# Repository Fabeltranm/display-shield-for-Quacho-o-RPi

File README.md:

# display-shield-for-Quacho-o-RPi

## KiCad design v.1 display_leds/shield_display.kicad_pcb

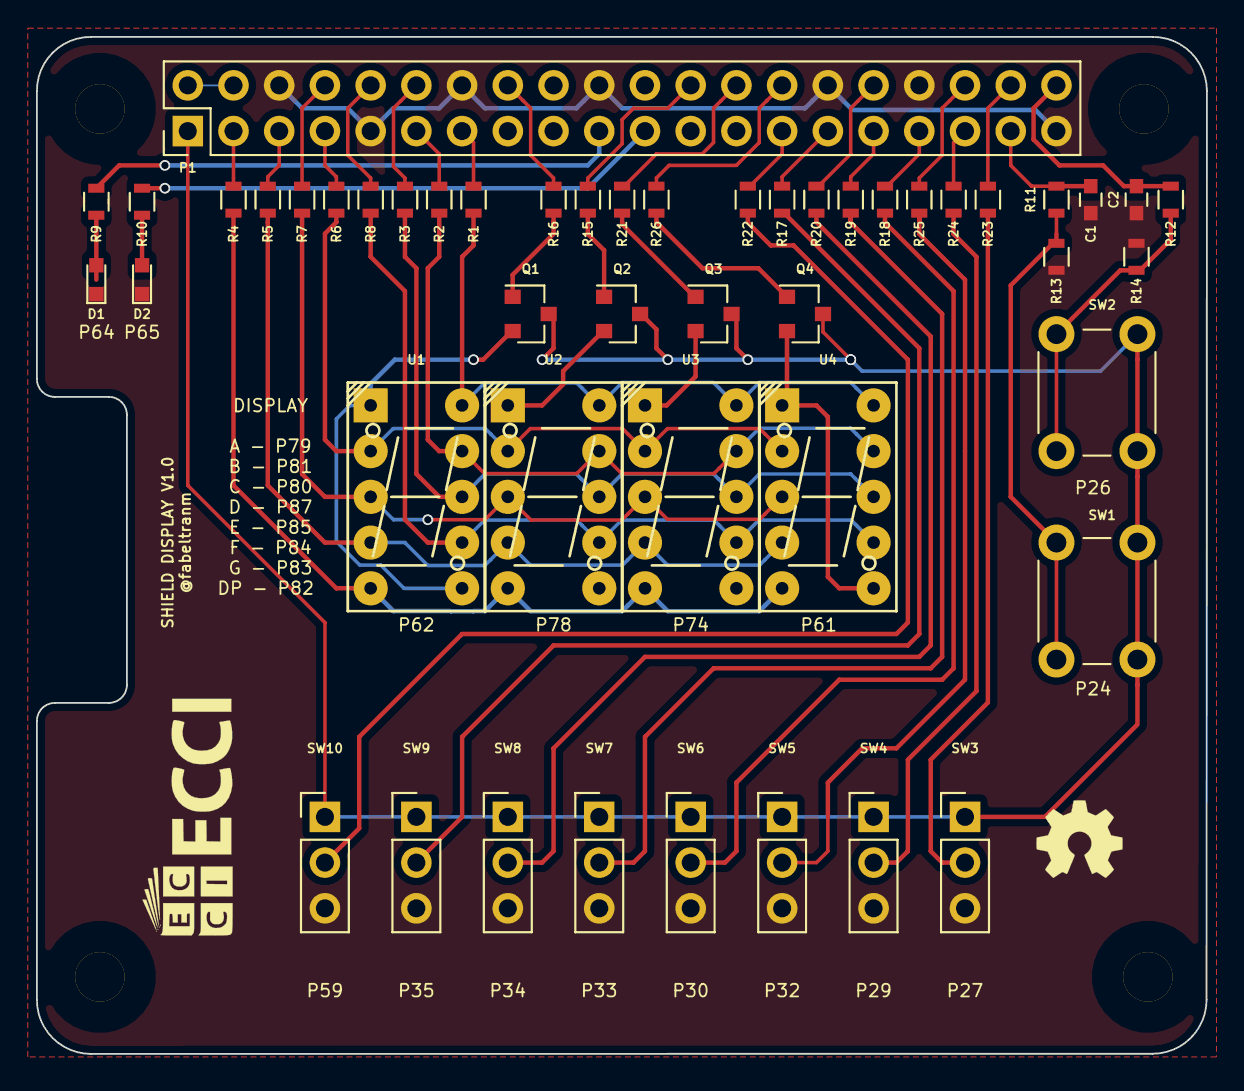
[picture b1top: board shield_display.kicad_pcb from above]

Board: 2 copper layers, 65.0 x 56.5 mm, 49 parts (0 on the bottom side), 55 nets.

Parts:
C1, C2: 0.1u; C_0603
D1, D2: LED; LED_0603
P1: CONN_02X20; Pin_Header_Straight_2x20_Pitch2.54mm
Q1, Q2, Q3, Q4: MMBT3906; SOT-23
R1, R2, R3, R4, R5, R6, R7, R8: 100; R_0603
R9, R10: 390; R_0603
R11, R12, R13, R14, R17, R18, R19, R20, R22, R23, R24, R25: 10K; R_0603
R15, R16, R21, R26: 2.2k; R_0603
SW1, SW2: PTS645SM43SMTR92 LFS; SW_PUSH_6mm
SW3, SW4, SW5, SW6, SW7, SW8, SW9, SW10: EG1218; Pin_Header_Straight_1x03_Pitch2.54mm
U1, U2, U3, U4: HDSP-7501; HDSP-78xx

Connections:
+3V3: P1.1, Q1.3, Q2.3, Q3.3, Q4.3, SW1.2, SW2.2, SW3.1, SW4.1, SW5.1, SW6.1, SW7.1, SW8.1, SW9.1, SW10.1
+5V: P1.2, P1.4
A: R1.1, U1.10, U2.10, U3.10, U4.10
B: R2.1, U1.9, U2.9, U3.9, U4.9
C: R3.1, U1.8, U2.8, U3.8, U4.8
D: R4.1, U1.5, U2.5, U3.5, U4.5
DP: R8.1, U1.7, U2.7, U3.7, U4.7
E: R5.1, U1.4, U2.4, U3.4, U4.4
F_: R6.1, U1.2, U2.2, U3.2, U4.2
G: R7.1, U1.3, U2.3, U3.3, U4.3
GND: C1.2, C2.2, D1.1, D2.1, P1.6, P1.9, P1.14, P1.20, P1.30, P1.34, P1.39, R13.1, R14.1, SW3.3, SW4.3, SW5.3, SW6.3, SW7.3, SW8.3, SW9.3, SW10.3
unnamed: D1.2, R9.1
unnamed: D2.2, R10.1
unnamed: Q1.1, R16.1
unnamed: Q1.2, U1.1, U1.6
unnamed: Q2.1, R15.1
unnamed: Q2.2, U2.1, U2.6
unnamed: Q3.1, R21.1
unnamed: Q3.2, U3.1, U3.6
unnamed: Q4.1, R26.1
unnamed: Q4.2, U4.1, U4.6
unnamed: R11.1, R13.2, SW1.1
unnamed: R12.1, R14.2, SW2.1
unnamed: R17.1, SW9.2
unnamed: R18.1, SW6.2
unnamed: R19.1, SW7.2
unnamed: R20.1, SW8.2
unnamed: R22.1, SW10.2
unnamed: R23.1, SW3.2
unnamed: R24.1, SW4.2
unnamed: R25.1, SW5.2
P024: C2.1, P1.40, R12.2
P026: C1.1, P1.37, R11.2
P027: P1.38, R23.2
P029: P1.35, R24.2
P030: P1.33, R18.2
P032: P1.36, R25.2
P033: P1.31, R19.2
P034: P1.32, R20.2
P035: P1.29, R17.2
P059: P1.27, R22.2
P061: P1.28, R26.2
P062: P1.24, R15.2
P064-DOUT(34): P1.19, R9.2
P065-DIN(35): P1.21, R10.2
P074: P1.26, R21.2
P078: P1.16, R16.2
P079: P1.13, R1.2
P080: P1.12, R3.2
P081: P1.11, R2.2
P082-TX_Pi: P1.10, R8.2
P083-RX_Pi: P1.8, R7.2
P084: P1.7, R6.2
P085: P1.5, R5.2
P087: P1.3, R4.2

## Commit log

2019-10-22 Add image in Readme file
2019-10-23 add display shield version 1
2019-10-23 add image to project
2019-10-31 Update gerber files
